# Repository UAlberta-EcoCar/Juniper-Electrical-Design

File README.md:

# Juniper-Electrical-Design - FOC Board

The FOC Board is planned to be on the car's steering wheel.
This branch currently contains the schematic and PCB files for the board.
For firmware see [https://github.com/UAlberta-EcoCar/Sally-Dashboard](https://github.com/UAlberta-EcoCar/Sally-Dashboard)

Board Requirements:
* A LCD screen with touch screen capabilities
* An IMU to track steering wheel position
* &gt; 3 Inputs for push buttons
* CAN FD capability 
* Addressable RGB LEDs
* Powered by a 7V and 12V power supply
* Overcurrent protection

MCU Chosen: STM32G491RET6

Link: https://www.digikey.ca/en/products/detail/stmicroelectronics/STM32G491RET6/13592591
* The STM32F4 series was considered, 
 but an MCU with the right stock options, clock speed, protocol support, and pin count was not found.

# Getting Started

Clone the repository:

```sh
git clone --recursive https://github.com/UAlberta-EcoCar/Juniper-Electrical-Design.git
```

Switch to the branch:

```sh
git checkout FOC-Board
```

Onboarding documentation here: [https://ualberta-ecocar.github.io/Documentation/](https://ualberta-ecocar.github.io/Documentation/)

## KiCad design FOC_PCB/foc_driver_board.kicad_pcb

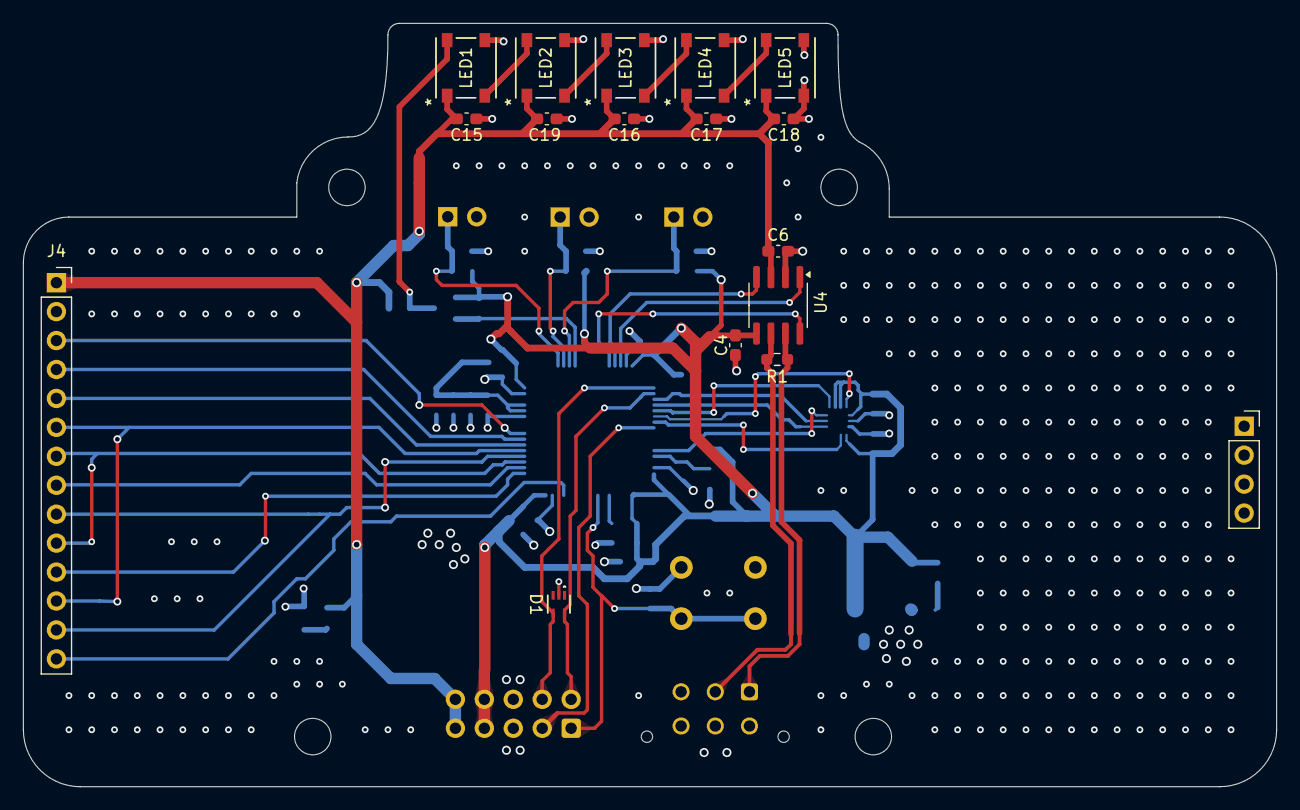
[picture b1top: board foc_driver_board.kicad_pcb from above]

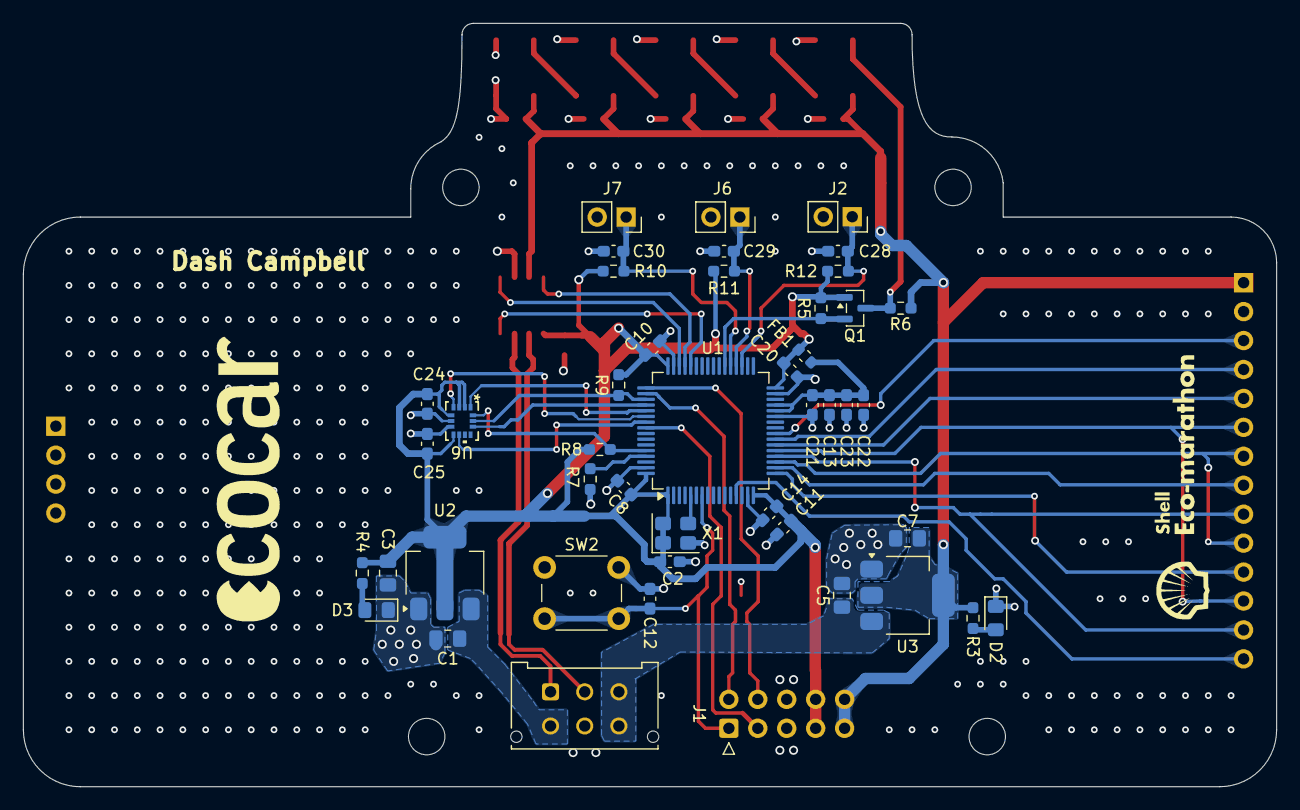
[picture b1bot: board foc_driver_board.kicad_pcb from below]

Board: 4 copper layers, 110.0 x 67.0 mm, 65 parts (45 on the bottom side), 43 nets.

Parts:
C1, C5: 10u; C_0805_2012Metric_Pad1.18x1.45mm_HandSolder
C2, C4, C8, C10, C12, C14, C15, C16, C17, C18, C19, C20, C21, C22, C24, C25, C28, C29, C30: 0u1; C_0603_1608Metric_Pad1.08x0.95mm_HandSolder
C3, C7: 22u; C_0805_2012Metric_Pad1.18x1.45mm_HandSolder
C6, C13, C23: 1u; C_0603_1608Metric_Pad1.08x0.95mm_HandSolder
C11: 4u7; C_0603_1608Metric_Pad1.08x0.95mm_HandSolder
D1: ESDALC6V1P5
D2, D3: LED; LED_0805_2012Metric_Pad1.15x1.40mm_HandSolder
FB1: FerriteBead; L_0603_1608Metric
H1, H2, H3, H4: MountingHole; MountingHole_3.2mm_M3
J1: STM32-Prog-Header; IDC-STM32-Prog-Header_2x05_P2.54mm_Vertical
J2, J6, J7: Conn_01x02_Pin; PinSocket_1x02_P2.54mm_Vertical
J3: Conn_01x06_Pin; STD_PWR_HEADER
J4: ST7796 DIsplay; ILI9488
LED1, LED2, LED3, LED4, LED5: COM-16347; COM-16347_SPK
Q1: BSS138; SOT-23
R1: 120R; R_0603_1608Metric_Pad0.98x0.95mm_HandSolder
R3, R4: 4k7; R_0603_1608Metric_Pad0.98x0.95mm_HandSolder
R5, R6, R7, R8, R9, R10, R11, R12: 10k; R_0603_1608Metric_Pad0.98x0.95mm_HandSolder
SW2: SW_Push; SW_PUSH_6mm
U1: STM32G491RET6; LQFP-64_10x10mm_P0.5mm
U2: AZ1117IH-3.3; SOT-223-3_TabPin2
U3: AZ1117IH-5.0; SOT-223-3_TabPin2
U4: MCP2542FD; SOIC-8_3.9x4.9mm_P1.27mm
U6: LSM6DSO32TR; LGA-14L_2P5X3X0P83_STM
X1: OXETDLJANF-8MHZ; Crystal_SMD_3225-4Pin_3.2x2.5mm

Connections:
+3.3VA: C13.1, C21.1, C22.1, C23.1, FB1.2, U1.28 (VREF+), U1.29 (VDDA)
+3V3: C2.1, C3.1, C4.1, C8.1, C10.1, C11.1, C14.1, C20.1, C24.1, C25.1, FB1.1, J1.7 (3.3V), J1.8 (3.3V), Q1.1 (G), R4.1, R5.1, R8.1, R9.1, R10.1, R11.1, R12.1, U1.1 (VBAT), U1.16 (VDD), U1.32 (VDD), U1.48 (VDD), U1.64 (VDD), U2.2 (VO), U4.5 (VIO), U6.2 (SDx), U6.3 (SCx), U6.5 (VDDIO), U6.8 (VDD), X1.1 (Tri-State), X1.4 (VDD)
+5V: C6.1, C7.1, C15.1, C16.1, C17.1, C18.1, C19.1, J1.9 (5V), J1.10 (5V), J4.1, LED1.1 (VDD), LED2.1 (VDD), LED3.1 (VDD), LED4.1 (VDD), LED5.1 (VDD), R3.1, R6.1, U3.2 (VO), U4.3 (VDD)
+7V: C1.1, J3.4, U2.3 (VI)
+12V: C5.1, J3.3, J3.6, U3.3 (VI)
/foc_driver_board/3V3_LED: D3.2 (A), R4.2
/foc_driver_board/5V_LED: D2.2 (A), R3.2
/foc_driver_board/DIN1: LED1.4 (DIN), Q1.3 (D), R6.2
/foc_driver_board/DIN2: LED1.2 (DOUT), LED2.4 (DIN)
/foc_driver_board/DIN3: LED2.2 (DOUT), LED3.4 (DIN)
/foc_driver_board/DIN4: LED3.2 (DOUT), LED4.4 (DIN)
/foc_driver_board/DIN5: LED4.2 (DOUT), LED5.4 (DIN)
/foc_driver_board/FDCAN+: J3.1, R1.2, U4.7 (CANH)
/foc_driver_board/FDCAN-: J3.2, R1.1, U4.6 (CANL)
/mcu/BOOT0: R7.1, U1.61 (PB8)
BTN1: C28.1, J2.1, R12.2, U1.35 (PB13)
BTN2: C29.1, J6.1, R11.2, U1.36 (PB14)
BTN3: C30.1, J7.1, R10.2, U1.37 (PB15)
FDCAN_RX: U1.45 (PA11), U4.4 (RXD)
FDCAN_STBY: U1.44 (PA10), U4.8 (STBY)
FDCAN_TX: U1.46 (PA12), U4.1 (TXD)
GNDA: C1.2, C2.2, C3.2, C4.2, C5.2, C6.2, C7.2, C8.2, C10.2, C11.2, C12.2, C13.2, C14.2, C15.2, C16.2, C17.2, C18.2, C19.2, C20.2, C21.2, C22.2, C23.2, C24.2, C25.2, C28.2, C29.2, C30.2, D1.2, D2.1 (K), D3.1 (K), J1.5 (GND), J1.6 (GND), J2.2, J3.5, J4.2, J6.2, J7.2, LED1.3 (VSS), LED2.3 (VSS), LED3.3 (VSS), LED4.3 (VSS), LED5.2 (DOUT), LED5.3 (VSS), R7.2, SW2.1, U1.15 (VSS), U1.27 (VSSA), U1.31 (VSS), U1.47 (VSS), U1.63 (VSS), U2.1 (GND), U3.1 (GND), U4.2 (VSS), U6.6 (GND), U6.7 (GND), X1.2 (GND)
IMU_CS: U1.52 (PC10), U6.12 (CS)
IMU_INT1: U1.54 (PC12), U6.4 (INT1)
IMU_INT2: U1.55 (PD2), U6.9 (INT2)
IMU_SA0: U1.53 (PC11), U6.1 (SDO/SA0)
IMU_SCL: R9.2, U1.51 (PA15), U6.13 (SCL)
IMU_SDA: R8.2, U1.60 (PB7), U6.14 (SDA)
LCD_BRIGHT: J4.8, U1.18 (PA4)
LCD_CS: J4.3, U1.24 (PB0)
LCD_DC: J4.5, U1.22 (PC4)
LCD_RESET: J4.4, U1.23 (PC5)
LED_IN: Q1.2 (S), R5.2, U1.38 (PC6)
NRST: C12.1, J1.1 (RST), SW2.2, U1.7 (PG10)
RCC: U1.5 (PF0), X1.3 (OUT)
SPI_MISO: J4.9, J4.13, U1.20 (PA6)
SPI_MOSI: J4.6, J4.12, U1.21 (PA7)
SPI_SCK: J4.7, J4.10, U1.19 (PA5)
SWCLK: D1.5, J1.2 (SWCLK), U1.50 (PA14)
SWDIO: D1.4, J1.4 (SWDIO), U1.49 (PA13)
SWO: J1.3 (SWIM), U1.56 (PB3)
T_CS: J4.11, U1.17 (PA3)
T_IRQ: J4.14, U1.13 (PA1)

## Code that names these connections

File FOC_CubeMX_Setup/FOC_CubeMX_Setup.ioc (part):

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Mcu.Name=STM32G491R(C-E)Tx
Mcu.Package=LQFP64
Mcu.UserName=STM32G491RETx
PA1.GPIOParameters=GPIO_Label
PA1.GPIO_Label=T_IRQ
PA1.Signal=GPXTI1
PA10.GPIOParameters=GPIO_Label
PA10.GPIO_Label=FDCAN_STBY
PA10.Signal=GPIO_Output
PA11.GPIOParameters=GPIO_PuPd
PA11.GPIO_PuPd=GPIO_PULLUP
PA11.Mode=FDCAN_Activate
PA11.Signal=FDCAN1_RX
PA12.Mode=FDCAN_Activate
PA12.Signal=FDCAN1_TX
PA13.Mode=Trace_Asynchronous_SW
PA13.Signal=SYS_JTMS-SWDIO
PA14.Mode=Trace_Asynchronous_SW
PA14.Signal=SYS_JTCK-SWCLK
PA15.GPIOParameters=GPIO_Label
PA15.GPIO_Label=IMU_SCL
PA15.Mode=I2C
PA15.Signal=I2C1_SCL
PA3.GPIOParameters=GPIO_Label
PA3.GPIO_Label=T_CS
PA3.Signal=GPIO_Output
PA4.GPIOParameters=GPIO_Label
PA4.GPIO_Label=LCD_BRIGHT
PA4.Signal=GPIO_Output
PA5.Mode=Full_Duplex_Master
PA5.Signal=SPI1_SCK
PA6.Mode=Full_Duplex_Master
PA6.Signal=SPI1_MISO
PA7.Mode=Full_Duplex_Master
PA7.Signal=SPI1_MOSI
PB0.GPIOParameters=GPIO_Label
PB0.GPIO_Label=LCD_CS
PB0.Signal=GPIO_Output
PB13.GPIOParameters=GPIO_Label
PB13.GPIO_Label=BTN1
PB13.Signal=GPXTI13
PB14.GPIOParameters=GPIO_Label
PB14.GPIO_Label=BTN2
PB14.Signal=GPXTI14
PB15.GPIOParameters=GPIO_Label
PB15.GPIO_Label=BTN3
PB15.Signal=GPXTI15
PB3.Mode=Trace_Asynchronous_SW
PB3.Signal=SYS_JTDO-SWO
PB7.GPIOParameters=GPIO_Label
PB7.GPIO_Label=IMU_SDA
PB7.Mode=I2C
PB7.Signal=I2C1_SDA
PC10.GPIOParameters=GPIO_Label
PC10.GPIO_Label=IMU_CS
PC10.Signal=GPIO_Output
PC11.GPIOParameters=GPIO_Label
PC11.GPIO_Label=IMU_SA0
PC11.Signal=GPIO_Output
PC12.GPIOParameters=GPIO_Label
PC12.GPIO_Label=IMU_INT1
PC12.Signal=GPXTI12
PC4.GPIOParameters=GPIO_Label
PC4.GPIO_Label=LCD_DC
PC4.Signal=GPIO_Output
PC5.GPIOParameters=GPIO_Label
PC5.GPIO_Label=LCD_RESET
PC5.Signal=GPIO_Output
PC6.GPIOParameters=GPIO_Label
PC6.GPIO_Label=LED_IN
PC6.Signal=S_TIM8_CH1
PD2.GPIOParameters=GPIO_Label
PD2.GPIO_Label=IMU_INT2
PD2.Signal=GPXTI2
PF0-OSC_IN.Mode=HSE-External-Clock-Source
PF0-OSC_IN.Signal=RCC_OSC_IN
RCC.HSE_VALUE=8000000
RCC.SYSCLKFreq_VALUE=170000000
RCC.SYSCLKSource=RCC_SYSCLKSOURCE_PLLCLK
board=custom

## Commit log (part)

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2026-06-06 Update README with project details and setup instructions
    Expanded project description and added onboarding instructions.
